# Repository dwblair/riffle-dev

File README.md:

# riffle-dev
dev repo for the riffle board

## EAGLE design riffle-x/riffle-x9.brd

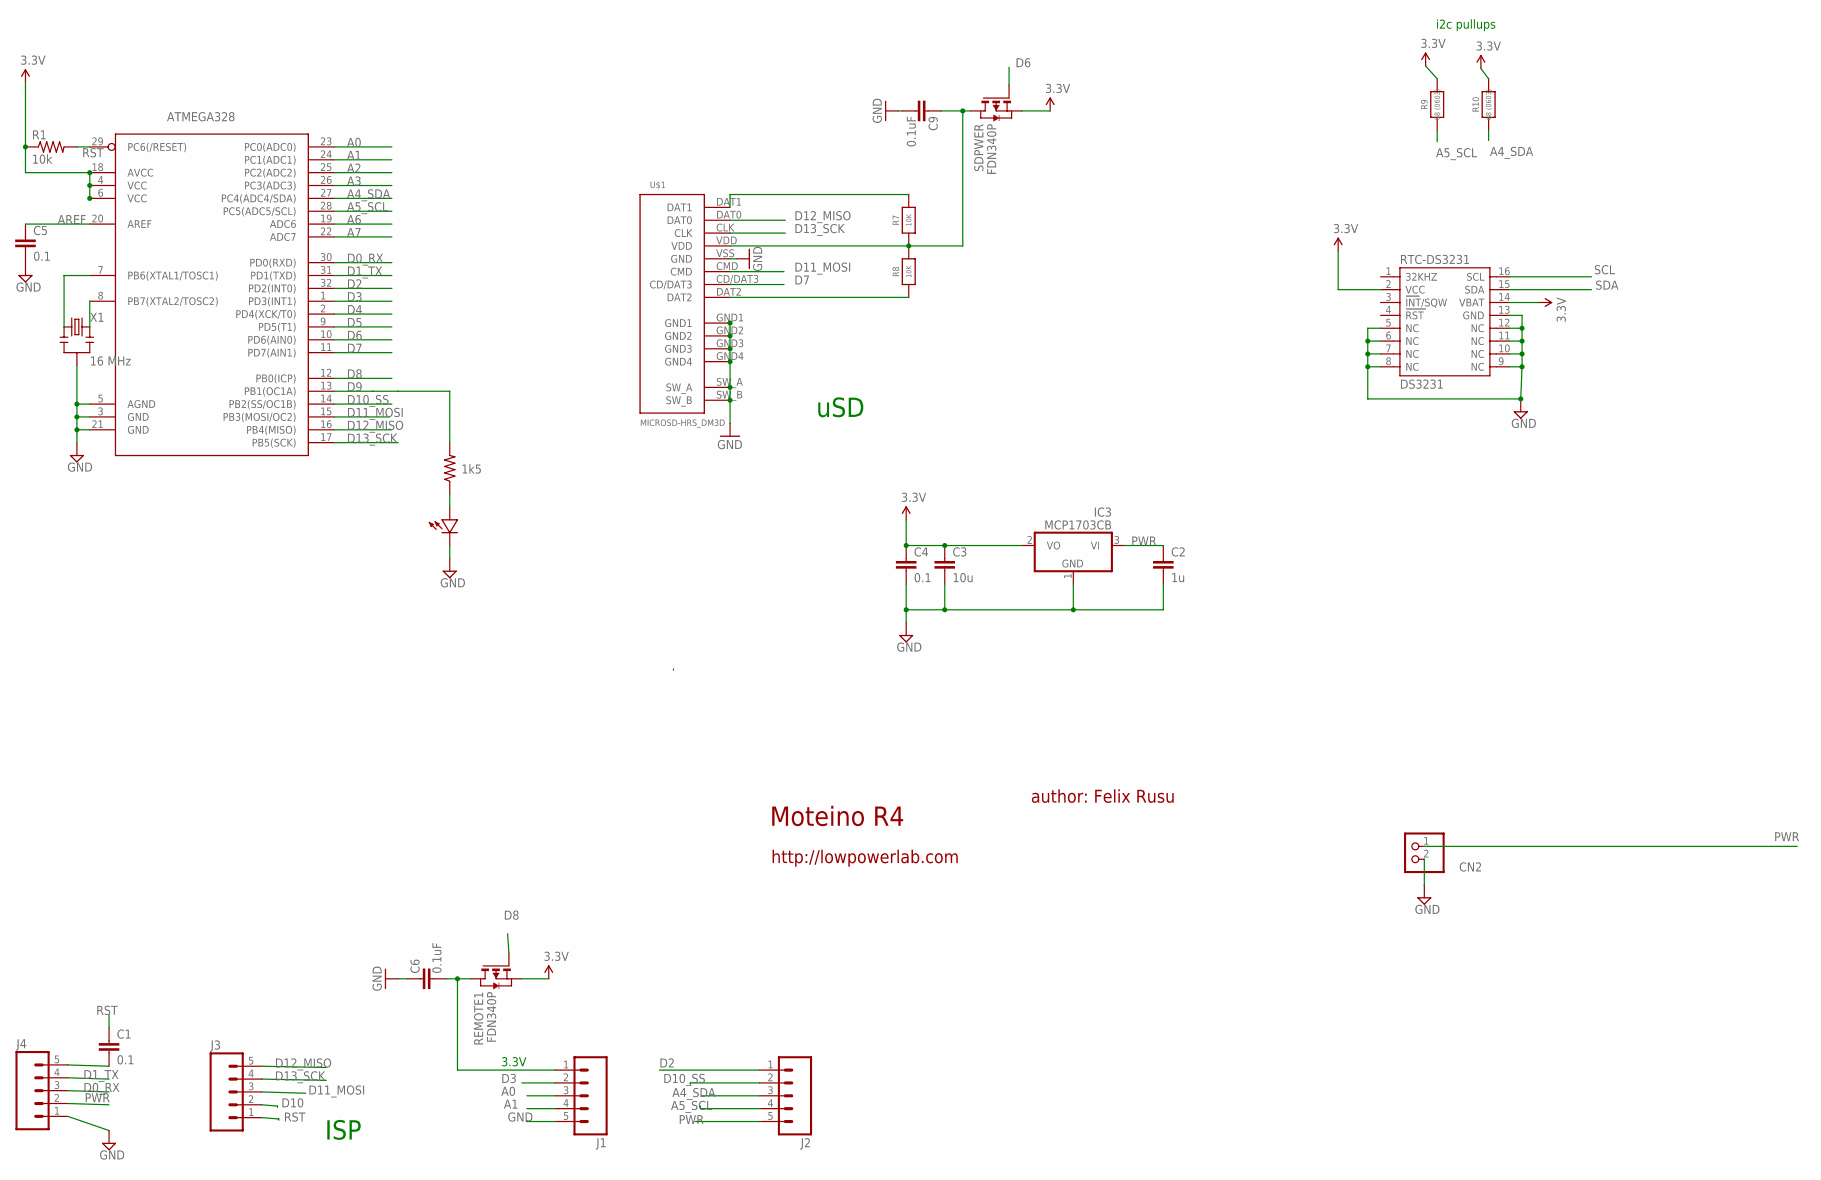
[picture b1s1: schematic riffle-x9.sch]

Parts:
ATMEGA328: ATMega-328; TQFP32-08
C1, C4, C5: 0.1; 0603-CAP
C2: 1u; 0603-CAP
C3: 10u; 0805-CAP
C6, C9: 0.1uF; 0603-CAP
CN2: JST_2PIN-SMT-RA; JST-PH-2-SMT-RA
IC3: MCP1703CB; SOT23
J1, J2, J3, J4: M051.27MM; 1X05-1.27MM
R1: 10k; 0603-RES
R2: 1k5; 0603-RES
R7, R8: 10K; 0603-NO
R9, R10: 68 (0603); 0603-NO
REMOTE1: FDN340P; SOT-23
RTC-DS3231: DS3231
SDPWER: FDN340P; SOT-23
U$1: MICROSD-HRS_DM3D; DM3D
U$2: LED0603; 0603-LED
X1: 16 MHz; RESONATOR-SMD

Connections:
A0: ATMEGA328.23 (PC0(ADC0)), J1.3
A1: ATMEGA328.24 (PC1(ADC1)), J1.4
A2: ATMEGA328.25 (PC2(ADC2))
A3: ATMEGA328.26 (PC3(ADC3))
A4_SDA: ATMEGA328.27 (PC4(ADC4/SDA)), J2.3, R10.1
A5_SCL: ATMEGA328.28 (PC5(ADC5/SCL)), J2.4, R9.1
A6: ATMEGA328.19 (ADC6)
A7: ATMEGA328.22 (ADC7)
AREF: ATMEGA328.20 (AREF), C5.1
D0_RX: ATMEGA328.30 (PD0(RXD)), J4.3
D1_TX: ATMEGA328.31 (PD1(TXD)), J4.4
D2: ATMEGA328.32 (PD2(INT0)), J2.1
D3: ATMEGA328.1 (PD3(INT1)), J1.2
D4: ATMEGA328.2 (PD4(XCK/T0))
D5: ATMEGA328.9 (PD5(T1))
D6: ATMEGA328.10 (PD6(AIN0)), SDPWER.3 (G)
D7: ATMEGA328.11 (PD7(AIN1)), U$1.CD/DAT3
D8: ATMEGA328.12 (PB0(ICP)), REMOTE1.3 (G)
D9: ATMEGA328.13 (PB1(OC1A)), R2.2
D10: J3.2
D10_SS: ATMEGA328.14 (PB2(SS/OC1B)), J2.2
D11_MOSI: ATMEGA328.15 (PB3(MOSI/OC2)), J3.3, U$1.CMD
D12_MISO: ATMEGA328.16 (PB4(MISO)), J3.5, U$1.DAT0
D13_SCK: ATMEGA328.17 (PB5(SCK)), J3.4, U$1.CLK
GND: ATMEGA328.3 (GND), ATMEGA328.5 (AGND), ATMEGA328.21 (GND), C2.2, C3.2, C4.2, C5.2, C6.2, C9.1, CN2.2 (1), IC3.1 (GND), J1.5, J4.1, RTC-DS3231.5 (NC), RTC-DS3231.6 (NC), RTC-DS3231.7 (NC), RTC-DS3231.8 (NC), RTC-DS3231.9 (NC), RTC-DS3231.10 (NC), RTC-DS3231.11 (NC), RTC-DS3231.12 (NC), RTC-DS3231.13 (GND), U$1.GND1, U$1.GND2, U$1.GND3, U$1.GND4, U$1.SW_A, U$1.SW_B, U$1.VSS (GND), U$2.MINUS, X1.2
unnamed: ATMEGA328.7 (PB6(XTAL1/TOSC1)), X1.1
unnamed: R2.1, U$2.PLUS
unnamed: C6.1, J1.1, REMOTE1.1 (D)
unnamed: C9.2, R7.1, R8.2, SDPWER.1 (D), U$1.VDD
unnamed: R7.2, U$1.DAT1
unnamed: R8.1, U$1.DAT2
unnamed: C1.2, J4.5
unnamed: ATMEGA328.8 (PB7(XTAL2/TOSC2)), X1.3
PWR: C2.1, CN2.1 (2), IC3.3 (VI), J2.5, J4.2
RST: ATMEGA328.29 (PC6(/RESET)), C1.1, J3.1, R1.2
SCL: RTC-DS3231.16 (SCL)
SDA: RTC-DS3231.15 (SDA)
VCC: ATMEGA328.4 (VCC), ATMEGA328.6 (VCC), ATMEGA328.18 (AVCC), C3.1, C4.1, IC3.2 (VO), R1.1, R9.2, R10.2, REMOTE1.2 (S), RTC-DS3231.2 (VCC), RTC-DS3231.14 (VBAT), SDPWER.2 (S)

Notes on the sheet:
Moteino R4
author: Felix Rusu
http://lowpowerlab.com
uSD
ISP
3.3V
i2c pullups

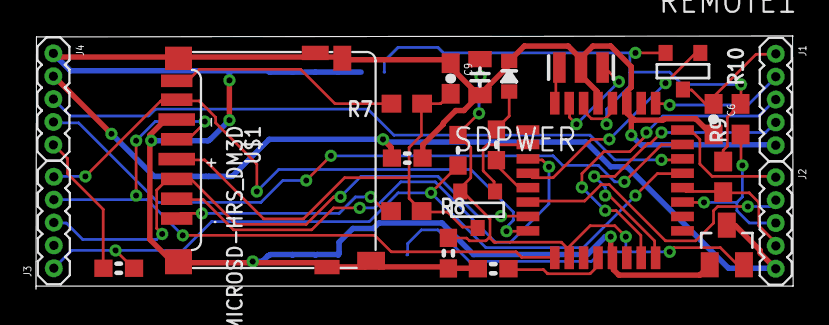
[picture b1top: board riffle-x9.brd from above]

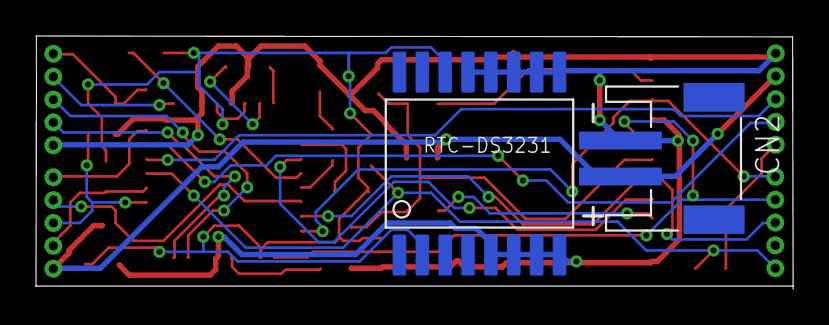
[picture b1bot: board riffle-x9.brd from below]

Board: 2 copper layers, 42.1 x 14.1 mm, 26 parts (2 on the bottom side), 29 nets.

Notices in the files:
parts and their libraries:
microbuilder: This work is placed in the public domain, and may be freely used for commercial and non-commercial work with the following conditions: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
SparkFun-Connectors: Licensing: Creative Commons ShareAlike 4.0 International - https://creativecommons.org/licenses/by-sa/4.0
